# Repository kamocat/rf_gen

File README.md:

# RF Generator
500W RF generator, tuned for 13.56MHz
Based on the paper [1kW Wideband Class E Power Amplifier](https://superlab.stanford.edu/publication/kw_mhz_wideband_class_e_power_amplifier_jiale/) from the Stanford Superlab.

I removed the duplicate circuit (for simplicity), added a FET driver, clock, and Arduino for control.

## Cost breakdown
| Category | Price | Description |
| --- | --- | --- |
| Assemblies | 19.95 | Arduino & Si5351 |
| Components | 47.25 | Parts that get soldered on |
| Consumables | 33.94 | Solder and magnet wire |
| Hardware | 4.89 | Screws, heatsink, thermal interface pad |
| PCB | 30.00 | From OSH Park. 2 oz copper |

## Electrical simulation
Simulation is done with LTSpice.
You will need the spice models for the [SiC mosfet](https://www.genesicsemi.com/sic-mosfet/G3R30MT12J/G3R30MT12J_SPICE.zip) and the [GaN mosfet](https://gansystems.com/wp-content/uploads/2020/02/GS61004B-Spice-Models-V4P2.zip)

## Thermal simulation
Simulation is done with Elmer / FreeCAD. Work in progress...

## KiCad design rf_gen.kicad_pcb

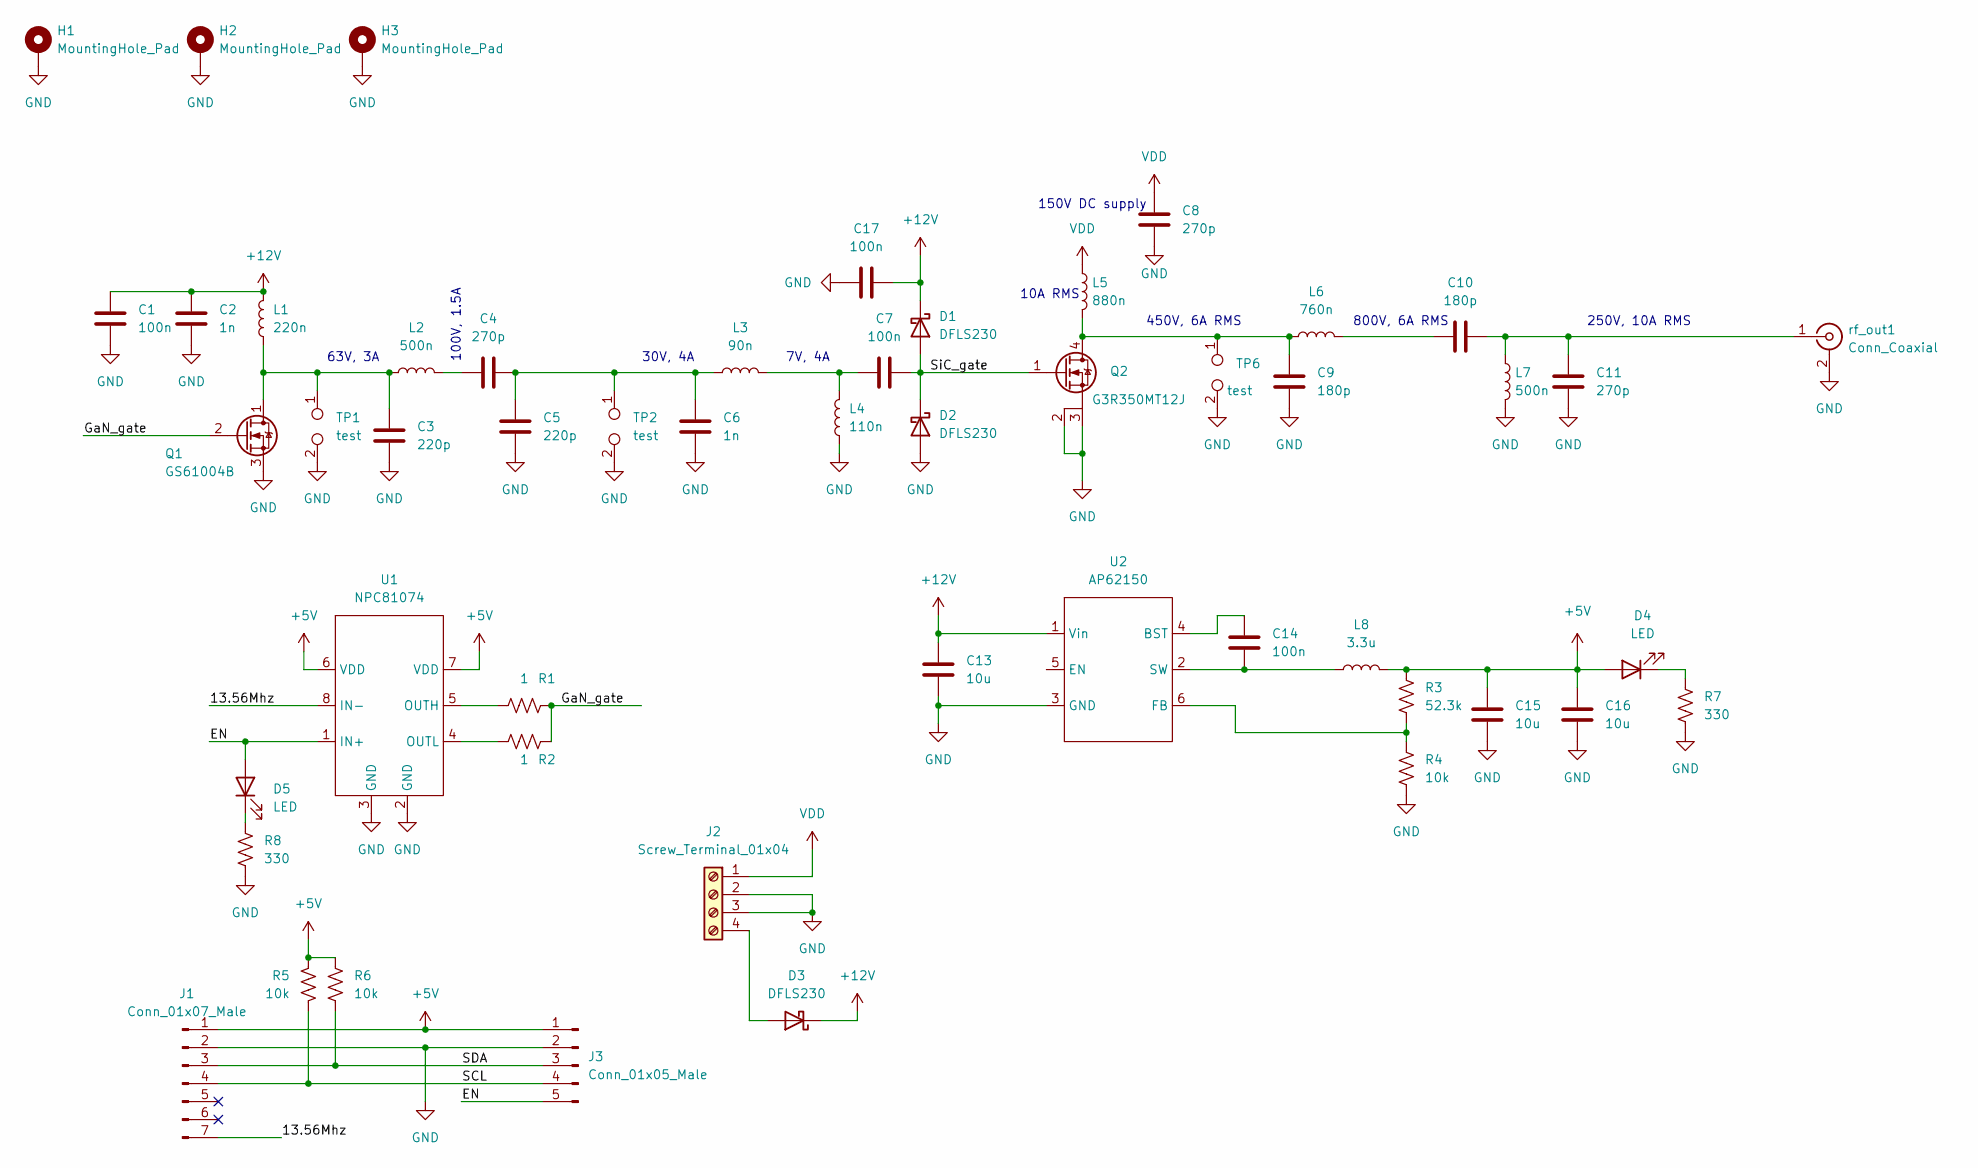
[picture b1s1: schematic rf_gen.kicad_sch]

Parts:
C1, C7, C17: 100n; C_1206_3216Metric
C2, C6: 1n; C_1210_3225Metric
C3, C5: 220p; C_1111_2828Metric
C4, C8, C11: 270p; C_1111_2828Metric
C9, C10: 180p; C_1111_2828Metric
C13, C15, C16: 10u; C_1206_3216Metric
C14: 100n; C_0805_2012Metric
D1, D2, D3: DFLS230; D_PowerDI-123
D4, D5: LED; LED_0805_2012Metric
H1, H2, H3: MountingHole_Pad; MountingHole_3.2mm_M3_Pad_Via
J1: Conn_01x07_Male; PinHeader_1x07_P2.54mm_Vertical
J2: Screw_Terminal_01x04; TerminalBlock_Phoenix_MKDS-1,5-4-5.08_1x04_P5.08mm_Horizont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
J3: Conn_01x05_Male; PinHeader_1x05_P2.54mm_Vertical
L1: 220n; 2222SQ-221
L2, L7: 500n; 2929SQ-501
L3: 90n; 2222SQ-90N
L4: 110n; 2222SQ-111
L5: 880n; inductor_air_15x15
L6: 760n; inductor_air_15x15
L8: 3.3u; L_0805_2012Metric
Q1: GS61004B; GaNpx
Q2: G3R350MT12J; TO-263-7_heatsink
R1, R2: 1; R_0805_2012Metric
R3: 52.3k; R_0805_2012Metric
R4, R5, R6: 10k; R_0805_2012Metric
R7, R8: 330; R_0805_2012Metric
TP1, TP2, TP6: test; TestPoint_2Pads_Pitch5.08mm_Drill1.3mm
U1: NPC81074; SOIC-8_3.9x4.9mm_P1.27mm
U2: AP62150; TSOT26
rf_out1: Conn_Coaxial; SMA_EdgeMount

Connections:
+5V: C15.1, C16.1, D4.2 (A), J1.1, J3.1, L8.2, R3.1, R5.2, R6.1, U1.6 (VDD), U1.7 (VDD)
+12V: C1.1, C2.2, C13.1, C17.2, D1.1 (K), D3.1 (K), L1.2, U2.1 (Vin)
/13.56Mhz: J1.7, U1.8 (IN-)
/EN: D5.2 (A), J3.5, U1.1 (IN+)
/GaN_gate: Q1.2 (G), R1.2, R2.2
/SCL: J1.4, J3.4, R5.1
/SDA: J1.3, J3.3, R6.2
/SiC_gate: C7.1, D1.2 (A), D2.1 (K), Q2.1 (G)
GND: C1.2, C2.1, C3.1, C5.2, C6.2, C8.1, C9.1, C11.2, C13.2, C15.2, C16.2, C17.1, D2.2 (A), H1.1, H2.1, H3.1, J1.2, J2.2, J2.3, J3.2, L4.1, L7.2, Q1.3 (S), Q2.2 (KS), Q2.3 (S), R4.2, R7.2, R8.2, TP1.2, TP2.2, TP6.2, U1.2 (GND), U1.3 (GND), U2.3 (GND), rf_out1.2 (Ext)
unnamed: C3.2, L1.1, L2.1, Q1.1 (D), TP1.1
unnamed: C4.1, L2.2
unnamed: C4.2, C5.1, C6.1, L3.1, TP2.1
unnamed: C7.2, L3.2, L4.2
unnamed: C9.2, L5.2, L6.1, Q2.4 (D), TP6.1
unnamed: C10.1, L6.2
unnamed: C10.2, C11.1, L7.1, rf_out1.1 (In)
unnamed: C14.1, U2.4 (BST)
unnamed: C14.2, L8.1, U2.2 (SW)
unnamed: D3.2 (A), J2.4
unnamed: D4.1 (K), R7.1
unnamed: D5.1 (K), R8.1
unnamed: R1.1, U1.5 (OUTH)
unnamed: R2.1, U1.4 (OUTL)
unnamed: R3.2, R4.1, U2.6 (FB)
VDD: C8.2, J2.1, L5.1

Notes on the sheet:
100V, 1.5A
63V, 3A
250V, 10A RMS
10A RMS
800V, 6A RMS
7V, 4A
450V, 6A RMS
30V, 4A
150V DC supply

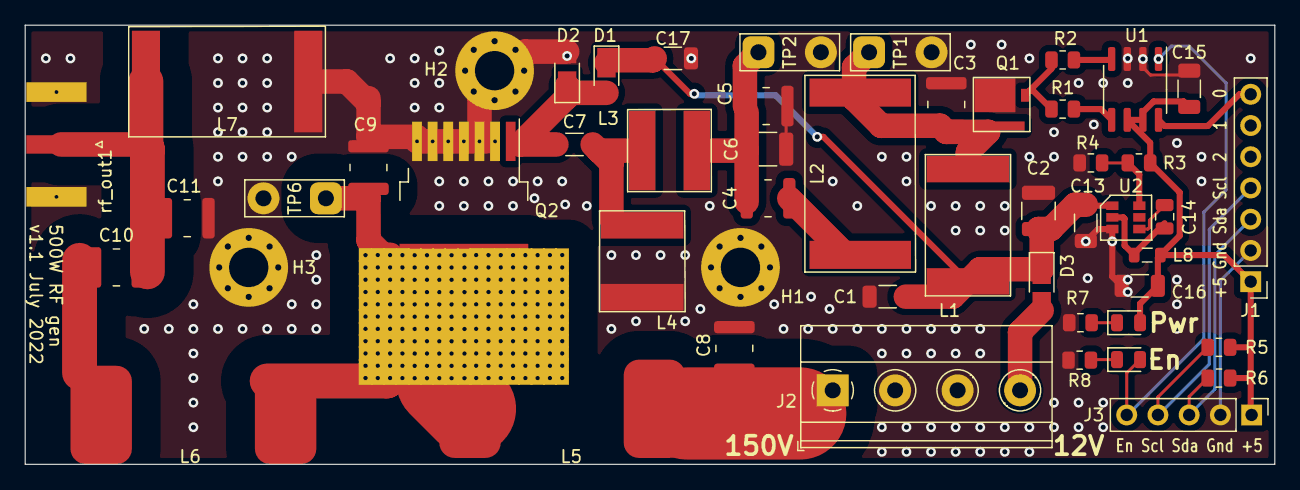
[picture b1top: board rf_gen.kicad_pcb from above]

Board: 2 copper layers, 101.6 x 35.7 mm, 51 parts (0 on the bottom side), 25 nets.

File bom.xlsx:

Designator | Package | Quantity | Designation | Supplier and ref | Price | Extended | Category | Notes
R2,R1 | R_0805_2012Metric | 2 | 1 | 667-ERJ-6GEYJ1R0V | 0.053999999999999999 | 0.108 | Component
R8,R7 | R_0805_2012Metric | 2 | 330 | 652-CR0805FX-3740ELF | 0.029000000000000001 | 0.058000000000000003 | Component
C14 | C_0805_2012Metric | 1 | 100n | 187-CL21B104KACNNNC | 0.028000000000000001 | 0.028000000000000001 | Component
C7,C1,C17 | C_1206_3216Metric | 3 | 100n | 81-GRM3195C1H104JA5D | 0.374 | 1.1219999999999999 | Component
R6,R4,R5 | R_0805_2012Metric | 3 | 10k | 603-RT0805FRE0710KL | 0.080000000000000002 | 0.23999999999999999 | Component
C16,C13,C15 | C_1206_3216Metric | 3 | 10u | 187-CL31B106MOHNNNE | 0.089999999999999997 | 0.27000000000000002 | Component
L4 | 2222SQ-111 | 1 | 110n | 994-2222SQ-111JEC | 1.8899999999999999 | 1.8899999999999999 | Component
C9,C10 | C_1111_2828Metric | 2 | 180p | https://www.mouser.com/ProductDetail/Vishay-Vitramon/VJ1111D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 | 1.0900000000000001 | 2.1800000000000002 | Component
C6,C2 | C_1210_3225Metric | 2 | 1n | 581-12105U102JAT2A | 0.68000000000000005 | 1.3600000000000001 | Component
L1 | 2222SQ-221 | 1 | 220n | 994-2222SQ-221JEC | 1.8500000000000001 | 1.8500000000000001 | Component
C5,C3 | C_1111_2828Metric | 2 | 220p | 77-VJ1111D221JXLAJ | 1.1299999999999999 | 2.2599999999999998 | Component
C8,C4,C11 | C_1111_2828Metric | 3 | 270p | 77-VJ1111D271JXLAJ | 1.3100000000000001 | 3.9300000000000002 | Component
L8 | L_0805_2012Metric | 1 | 3.3u | 810-MLZ2012M3R3HT000 | 0.17000000000000001 | 0.17000000000000001 | Component
L7,L2 | 2929SQ-501 | 2 | 500n | https://www.mouser.com/ProductDetail/Coilcraft/2929SQ-501JEC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 | 2.0699999999999998 | 4.1399999999999997 | Component
R3 | R_0805_2012Metric | 1 | 52.3k | 603-RT0805FRE0752K3L | 0.081000000000000003 | 0.081000000000000003 | Component
L6 | inductor_air_15x15 | 1 | 760n | N/A | 0 | 0 | Component | Hand-wind, plastic 15mm core
L5 | inductor_air_15x15 | 1 | 880n | N/A | 0 | 0 | Component | Hand-wind, plastic 15mm core
L3 | 2222SQ-90N | 1 | 90n | 994-2222SQ-90NJEC | 1.8500000000000001 | 1.8500000000000001 | Component
U2 | TSOT26 | 1 | AP62150 | 621-AP62150WU-7 | 0.44 | 0.44 | Component
J3 | PinHeader_1x05_P2.54mm_Vertical | 1 | Conn_01x05_Male | 782-ABX00028 | 12 | 12 | Component
J1 | PinHeader_1x07_P2.54mm_Vertical | 1 | Conn_01x07_Male | 485-2045 | 7.9500000000000002 | 7.9500000000000002 | Component
rf_out1 | SMA_EdgeMount | 1 | Conn_Coaxial | 712-CONSMA020.062-G | 3.9300000000000002 | 3.9300000000000002 | Component
D2,D3,D1 | D_PowerDI-123 | 3 | DFLS230 | 621-DFLS230-7 | 0.69999999999999996 | 2.0999999999999996 | Component
Q2 | TO-263-7_heatsink | 1 | G3R350MT12J | 905-G3R350MT12J | 6.0599999999999996 | 6.0599999999999996 | Component
Q1 | GaNpx | 1 | GS61004B | 499-GS61004B-MR | 7.2199999999999998 | 7.2199999999999998 | Component
D4,D5 | LED_0805_2012Metric | 2 | LED | 710-150080GS75000 | 0.019 | 0.037999999999999999 | Component
H3,H1,H2 | MountingHole_3.2mm_M3_Pad_Via | 3 | MountingHole_Pad | 728-062809-008 | 0.050000000000000003 | 0.15000000000000002 | Hardware
U1 | SOIC-8_3.9x4.9mm_P1.27mm | 1 | NPC81074 | 863-NCP81074ADR2G | 1.6299999999999999 | 1.6299999999999999 | Component
J2 | TerminalBlock_Phoenix_MKDS-1,5-4-5.08_1x04_P5.08mm_Horizontal | 1 | Screw_Terminal_01x04 | 649-220316-H041B01LF | 0.89000000000000001 | 0.89000000000000001 | Component
TP6,TP1,TP2 | TestPoint_2Pads_Pitch5.08mm_Drill1.3mm | 3 | test | N/A | 0 | 0 | Component | For oscope probe
 | #16 Magnet Wire | 1 |  | Amazon | 11.449999999999999 | 11.449999999999999 | Consumable
 | Heat sink | 1 |  | HSB21-454515 | 2.1099999999999999 | 2.1099999999999999 | Hardware
 | PCB | 1 |  | OSH Park | 10 | 30 | PCB
 | Solder paste | 1 |  | 4902P-15G | 11.039999999999999 | 11.039999999999999 | Consumable
 | Thermal Interface Pad | 1 |  | 588-HS100-TP2 | 2.6299999999999999 | 2.6299999999999999 | Hardware
 | Shipping |  |  |  |  | 7.9900000000000002
 |  |  |  |  |  | 129.16499999999999

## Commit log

2022-06-23 First draft of schematic
2022-06-23 Added Mouser BOM
2022-06-24 Added CoilCraft footprints
    Using approximate footprints for the toroids for now
2022-06-24 First draft of PCB layout
2022-06-24 Added simulation and design notes
2022-07-05 Added netclasses, test points, fixed buck regulator
2022-07-05 Draft of trace routing
2022-07-05 Finished routing
    Replaced power inductor footprints with actual sizes
    Placed test points that seemed useful, removed ones that didn't fit
    Replaced RF connector and power input connectors
    Added LED to indicate power
    Added stitching vias
2022-07-06 Added KiCAD BOM
2022-07-06 Added heatsink
    Switched power inductors to surface-mount to avoid shorting
    Added silkscreen text for connectors and LEDs
2022-07-06 Finishing touches
    Fixed design violations. Had to make exceptions for 1kV due to the dimensions of the parts
    Added top and front views of PCB
2022-07-08 Added 3D models for footprints
2022-07-08 Added heatsink, improved eq core windings
2022-07-16 Added GaN FET model to SPICE sim
2022-07-16 Removed thermal reliefs on GND plane
2022-07-16 Updated PCB due to inductor changes
2022-07-16 Changed L2 to use CoilCraft inductor
2022-07-16 Fixed DRC issues
    Buck regulator was wired incorrectly. Not sure how this happened.
    Increased spacing between pads on RF capacitor to reduce chance of arcing
2022-07-16 Updated BOM to reflect cost reductions
    Removed ferrite cores from inductors
    Changed L2 and L7 to standard parts
    Consolidated some capacitor values
2022-07-16 Updated Coilcraft models for accuracy
2022-07-16 Added 3d model for toroid inductor
2022-07-16 Fixed board stackup dimensions
2022-07-16 Changed output filter to handle lower impedance
